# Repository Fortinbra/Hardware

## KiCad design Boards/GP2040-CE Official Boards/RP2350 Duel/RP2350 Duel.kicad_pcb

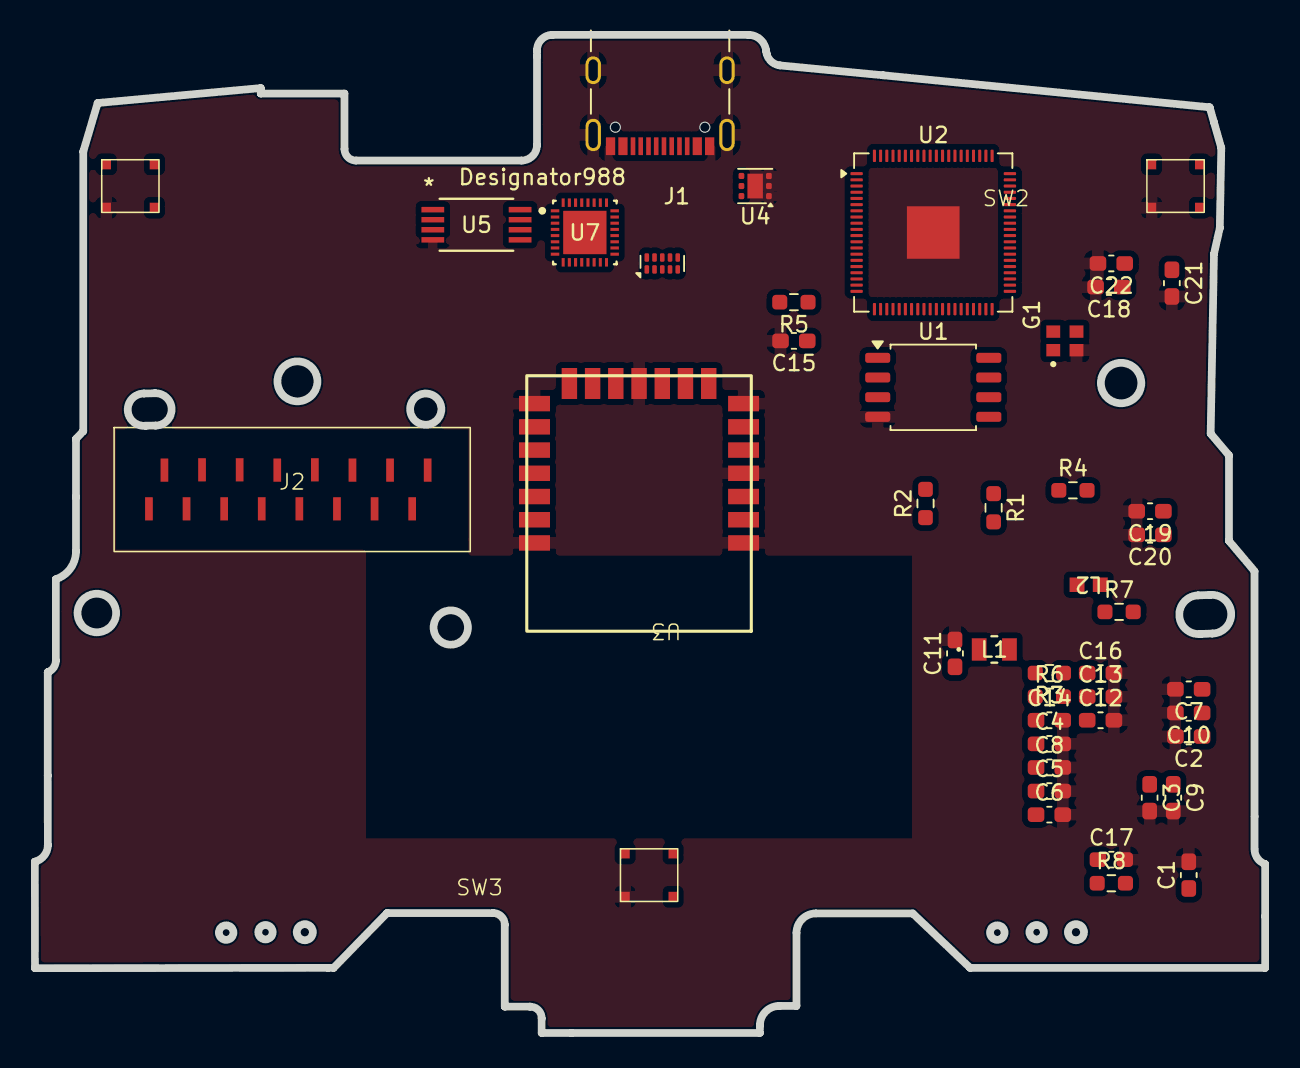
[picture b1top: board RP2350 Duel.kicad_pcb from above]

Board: 4 copper layers, 79.5 x 64.5 mm, 45 parts (0 on the bottom side), 50 nets, no tracks yet.

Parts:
C1, C2, C3, C4, C5, C6, C7, C8, C9, C10, C15, C16: 100nF; C_0603_1608Metric_Pad1.08x0.95mm_HandSolder
C11, C13: 10uF; C_0603_1608Metric_Pad1.08x0.95mm_HandSolder
C12, C14: 2.2uF; C_0603_1608Metric_Pad1.08x0.95mm_HandSolder
C17: 0.1uF; C_0603_1608Metric_Pad1.08x0.95mm_HandSolder
C18, C19, C20: C_Small; C_0603_1608Metric_Pad1.08x0.95mm_HandSolder
C21, C22: 330pF; C_0603_1608Metric_Pad1.08x0.95mm_HandSolder
G1: SiT8008BI-72-33N-12.000000; OSC_SiT8008BI-72-33N-12.000000
J1: UJ20-C-H-G-SMT-2A-P16-TR; SAMESKY_UJ20-C-H-G-SMT-2A-P16-TR
J2: Conn_02x08_Odd_Even; FlexPCB
L1: MLZ2012M3R3HT000; IND_2012_TDK
L2: BLM18EG471SN1D; IND_BLM18_0603_MUR
R1, R2: 1k; R_0603_1608Metric_Pad0.98x0.95mm_HandSolder
R3: 220R; R_0603_1608Metric_Pad0.98x0.95mm_HandSolder
R4: 10k; R_0603_1608Metric_Pad0.98x0.95mm_HandSolder
R5: 470R; R_0603_1608Metric_Pad0.98x0.95mm_HandSolder
R6: 27R4; R_0603_1608Metric_Pad0.98x0.95mm_HandSolder
R7, R8: 4.7k; R_0603_1608Metric_Pad0.98x0.95mm_HandSolder
SW1, SW2, SW3: SW_SPST; SKRWAEE030
U1: W25Q128JVS; SOIC-8_5.3x5.3mm_P1.27mm
U2: RP2350B; QFN-80-1EP_10x10mm_P0.4mm_EP3.4x3.4mm
U3: RM2
U4: TVS2200DRV; WSON-6-1EP_2x2mm_P0.65mm_EP1x1.6mm
U5: 24LC512
U6: TPD4EUSB30; USON-10_2.5x1.0mm_P0.5mm
U7: TPS25751SRSMR; RSM0032B-MFG

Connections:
+1V1: C1.1, C2.1, C3.1, C4.1, C5.1, C6.1, C7.1, C11.1, L1.2, U2.5 (IOVDD), U2.15 (IOVDD), U2.24 (IOVDD), U2.29 (IOVDD), U2.41 (IOVDD), U2.50 (IOVDD), U2.60 (IOVDD), U2.65 (VREG_FB), U2.76 (IOVDD)
+3.3V: C15.1, C17.1, L2.2, R2.1, R7.1, R8.1, U1.8 (VCC), U5.8 (VCC)
/ADC_AVDD: C14.1, U2.59 (ADC_AVDD)
/ADC_VREF: C12.1, R3.2, R6.2, U2.61 (VREG_AVDD)
/CIR: J2.14, U2.4 (GPIO7)
/DOWN: J2.1, U2.80 (GPIO3)
/DVDD: C8.1, C9.1, C10.1, U2.10 (DVDD), U2.32 (DVDD), U2.51 (DVDD)
/L1: J2.6, U2.12 (GPIO13)
/L2: J2.7, U2.7 (GPIO9)
/LEFT: J2.4, U2.2 (GPIO5)
/MUTE: SW3.1 (A), U2.20 (GPIO20)
/Power/CC1: C21.1, J1.A5 (CC1), U7.24 (CC1)
/Power/CC2: C22.1, J1.B5 (CC2), U7.25 (CC2)
/Power/D+: J1.A6 (DP1), J1.B6 (DP2), U6.1 (D1+)
/Power/D-: J1.A7 (DN1), J1.B7 (DN2), U6.2 (D1-)
/Power/VBUS: C18.1, J1.A4_B9 (VBUS), J1.B4_A9 (VBUS__1), U4.4 (IN), U4.5 (IN), U4.6 (IN), U7.26 (VBUS), U7.27 (VBUS)
/QSPI_SCLK: U1.6 (CLK), U2.71 (QSPI_SCLK)
/QSPI_SD0: U1.5 (DI/IO_{0}), U2.72 (QSPI_SD0)
/QSPI_SD1: U1.2 (DO/IO_{1}), U2.74 (QSPI_SD1)
/QSPI_SD2: U1.3 (~WP/IO_{2}), U2.73 (QSPI_SD2)
/QSPI_SD3: U1.7 (~HOLD/~RESET/IO_{3}), U2.70 (QSPI_SD3)
/QSPI_SS: R1.1, U1.1 (~CS), U2.75 (~QSPI_SS)
/R1: J2.10, U2.11 (GPIO12)
/R2: J2.9, U2.6 (GPIO8)
/RIGHT: J2.3, U2.1 (GPIO4)
/SELECT: SW1.1 (A), U2.16 (GPIO16)
/SQ: J2.12, U2.8 (GPIO10)
/START: SW2.1 (A), U2.17 (GPIO17)
/TR: J2.13, U2.9 (GPIO11)
/UP: J2.5, U2.79 (GPIO2)
/USB_DN: U2.66 (USB_DM), U6.5 (D2-)
/USB_DP: U2.67 (USB_DP), U6.4 (D2+)
/VDDIO: L2.1, U3.14 (VDDIO), U3.16 (VIN)
/VREG_LX: L1.1, U2.63 (VREG_LX)
/VREG_VIN: C13.1, R6.1, U2.64 (VREG_VIN)
/WL_D: R4.1, R5.2, U2.25 (GPIO24), U3.6 (gSPI_Data_Out)
/WL_ON: U2.23 (GPIO23), U3.12 (Wi-Fi_ON), U3.13 (BT_ON)
/X: J2.15, U2.3 (GPIO6)
/XIN: G1.3 (OUT), U2.30 (XIN)
/gSPI_CS: U2.26 (GPIO25), U3.9 (gSPI_CS)
/gSPI_Data_In: R5.1, U3.5 (gSPI_Data_In)
/gSPI_SCLK: U2.37 (GPIO29), U3.3 (gSPI_SCLK)
/nIRQ: R4.2, U3.10 (nIRQ)
GND: C1.2, C2.2, C3.2, C4.2, C5.2, C6.2, C7.2, C8.2, C9.2, C10.2, C11.2, C12.2, C13.2, C14.2, C15.2, C16.2, C17.2, C18.2, C19.2, C20.2, C21.2, C22.2, G1.2 (GND), J1.A1_B12 (GND), J1.B1_A12 (GND__1), J1.SH1 (SHIELD), J1.SH2 (SHIELD__1), J1.SH3 (SHIELD__2), J1.SH4 (SHIELD__3), J2.2, J2.11, SW1.2 (B), SW2.2 (B), SW3.2 (B), U1.4 (GND), U2.62 (VREG_PGND), U2.81 (GND), U3.1 (GND), U3.4 (GND), U3.7 (GND), U3.11 (GND), U3.15 (GND), U3.21 (GND), U4.1 (GND), U4.2 (GND), U4.3 (GND), U4.7 (GND), U5.4 (GND), U5.7 (WP), U6.3 (GND), U6.8 (GND), U7.11 (GND), U7.12 (GND), U7.14 (GND), U7.33 (GND)
unnamed: C16.1, R3.1
unnamed: G1.4 (VDD), R2.2
unnamed: R8.2, U5.6 (SCL), U7.16 (I2Cc_SCL)
unnamed: R7.2, U5.5 (SDA), U7.15 (I2Cc_SDA)
unnamed: C20.1, U7.4 (LDO_1V5)
unnamed: C19.1, U7.1 (LDO_3V3)

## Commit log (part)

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2026-06-08 Adding PGA2350 and RM2 module KiCad footprints and symbols
2026-06-22 adding new Duel board
2026-06-28 Clear used designators in RP2350 Duel board file
